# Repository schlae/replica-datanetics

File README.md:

# Replica Datanetics Keyboard

Do you need a Datanetics ASCII keyboard for your computer project (such as a replica Apple 1)? Don't want to pay high prices for an original Datanetics keyboard? Then consider building this replica.

This is not the first replica Datanetics keyboard. Mike Willegal [designed one](http://www.willegal.net/appleii/apple1-datanetics.htm). In fact, I started with his design and redid it using KiCad. Instead of using the expensive, fragile, and hard-to-find MM5740 keyboard chip, I switched to a more common microcontroller: the ATMega644P. I also removed the output buffer chips--just in case you want to redo my firmware and implement some other keyboard protocol, you'll be able to control the pin direction.

Here are the design files. The BOM does not include manufacturer part numbers because it uses very common through hole parts that you might already have. The key switches are standard Cherry MX and are available from a wide variety of sources.

[Schematic](https://github.com/schlae/replica-datanetics/blob/main/Apple1Keyb.pdf)

[Bill of Materials](https://github.com/schlae/replica-datanetics/blob/main/Apple1Keyb.csv)

[Fab Files](https://github.com/schlae/replica-datanetics/blob/main/fab/Apple1Keyb_Rev1.zip)

[Water Slide Decal Graphics](https://github.com/schlae/replica-datanetics/blob/main/keycaps.svg)

## Fabrication and Assembly Notes

The circuit board is a 2-layer board, 11.75 by 5.5 inches (298.5 x 139.7mm). No special edge connector plating or bevel is needed. To make the board look like the original, order the board "bare bones" with no solder mask or silkscreen.

**Caution: There is a "matrix" via area in the upper left corner of the board with 76 non-plated vias. The drill locations for these are included in the "Apple1Keyb-NPTH.drl" file in the fab package. The User Comments layer also includes a note to the fab vendor to NOT plate these holes. You may want to add an extra comment to your fab vendor when you put in the order that these 76 holes must not be plated.**

To assemble the board, just solder in the components. I'd recommend using a socket for the U1 microcontroller so that you can reprogram it later. The NE555 timer (U2) in the original design was meant to provide the clock for the MM5740 chip, but isn't necessary in this design. You can install it or leave it out.

The second NE555 timer (U3) is necessary for the key repeat function.

## Key Caps

The keyboard design uses standard Cherry MX key switches and keycaps are available from numerous sources. For my own build, I used DSA keycaps along with an 8U spacebar from PMK. I looked into a number of ways of putting the legends on the keycaps but I ended up having some water slide decals custom made. See the file above if you want to use this same file, but I'd recommend putting the legends closer together so they'll fit on a smaller sheet, saving you money.

## Matrix Via Area

The Datanetics design has four key switches that are not connected to the key scanning matrix and are brought out to individual pins on the edge connector. If you're building an Apple 1, you'll want to use two of these keys for the reset and clear screen functions. 

If you want keys to be included in the scanning matrix, you'll want to solder a fine wire through the appropriate via in the upper left corner of the board. To find out which key will be generated, look up the row and column number in the key\_rom array in firmware source code. You can, of course, customize the generated key by editing the source and recompiling.

## Firmware

The firmware is designed for the ATMega644P microcontroller, but it should be possible to modify it to work with other 40-pin microcontrollers in the ATMega family. The prebuilt firmware behaves like a stock MM5740.

[Prebuilt Firmware](https://github.com/schlae/replica-datanetics/blob/main/fw/apple1keyb.hex)

Be sure to set the fuse bits of the ATMega644P according to the fuses.conf file:

```
lfuse = 0x62
hfuse = 0xdd
efuse = 0xfc
```

You can build the firmware yourself pretty easily. Under Ubuntu, install the `gcc-avr` package, and build the firmware by going to the directory and typing `make`.

If you have a minipro programmer (TL866 etc) you can program the device by typing `make fuses` followed by `make prog`. For this to work correctly, you'll need the [minipro software](https://gitlab.com/DavidGriffith/minipro) installed. You could also use the Windows minipro software from the manufacturer, or another programmer entirely.

## Mechanical Brackets

[Mike Willegal's site](http://www.willegal.net/appleii/apple1-datanetics.htm) has drawings for a mechanical bracket.

## Connecting to an Apple 1

If you want to connect this keyboard to an Apple 1, you can use the following wiring diagram. The connector to use is a 30-pin 0.156" edge connector, something like EDAC 305-030-520-202 or equivalent. The DIP plug is an insulation displacement connector, something like CW CWR-130-16-0001 or equivalent.

| Edge connector pin | Description | DIP plug pin |
|--------------------|-------------|--------------|
| A | No connect (was -12V) | 11 (-12V) |
| B | Data bit 6 | 7 (B6) |
| C | Data bit 5 | 6 (B5) |
| D | Data bit 4 | 2 (B4) |
| E | Data bit 1 | 5 (B1) |
| F | Data bit 2 | 4 (B2) |
| H | Data bit 3 | 3 (B3) |
| J | Reset key | 1 (Reset) |
| K | Reset key | 9 (Gnd) |
| L | No connect (was OE) | No connect |
| M | Strobe | 14 (Str) |
| N | Data bit 7 | 8 (B7) |
| P | Data bit 8 | No connect |
| R | No connect (was data bit 9) | No connect |
| S | Ground | 9 |
| 1 | No connect | |
| 2 | No connect | |
| 3 | No connect | |
| 4 | +5V | 15, 16 |
| 5 | No connect | |
| 6 | No connect | |
| 7 | No connect | |
| 8 | Extra key 4 | 12 (Clr) |
| 9 | Extra key 4 | 16 |
| 10 | Extra key 3 | |
| 11 | Extra key 3 | |
| 12 | Extra key 1 | |
| 13 | Extra key 1 | |
| 14 | Extra key 2 | |
| 15 | Extra key 2 | |

## License
This work is licensed under a Creative Commons Attribution-ShareAlike 4.0
International License. See [https://creativecommons.org/licenses/by-sa/4.0/](https://creativecommons.org/licenses/by-sa/4.0/).

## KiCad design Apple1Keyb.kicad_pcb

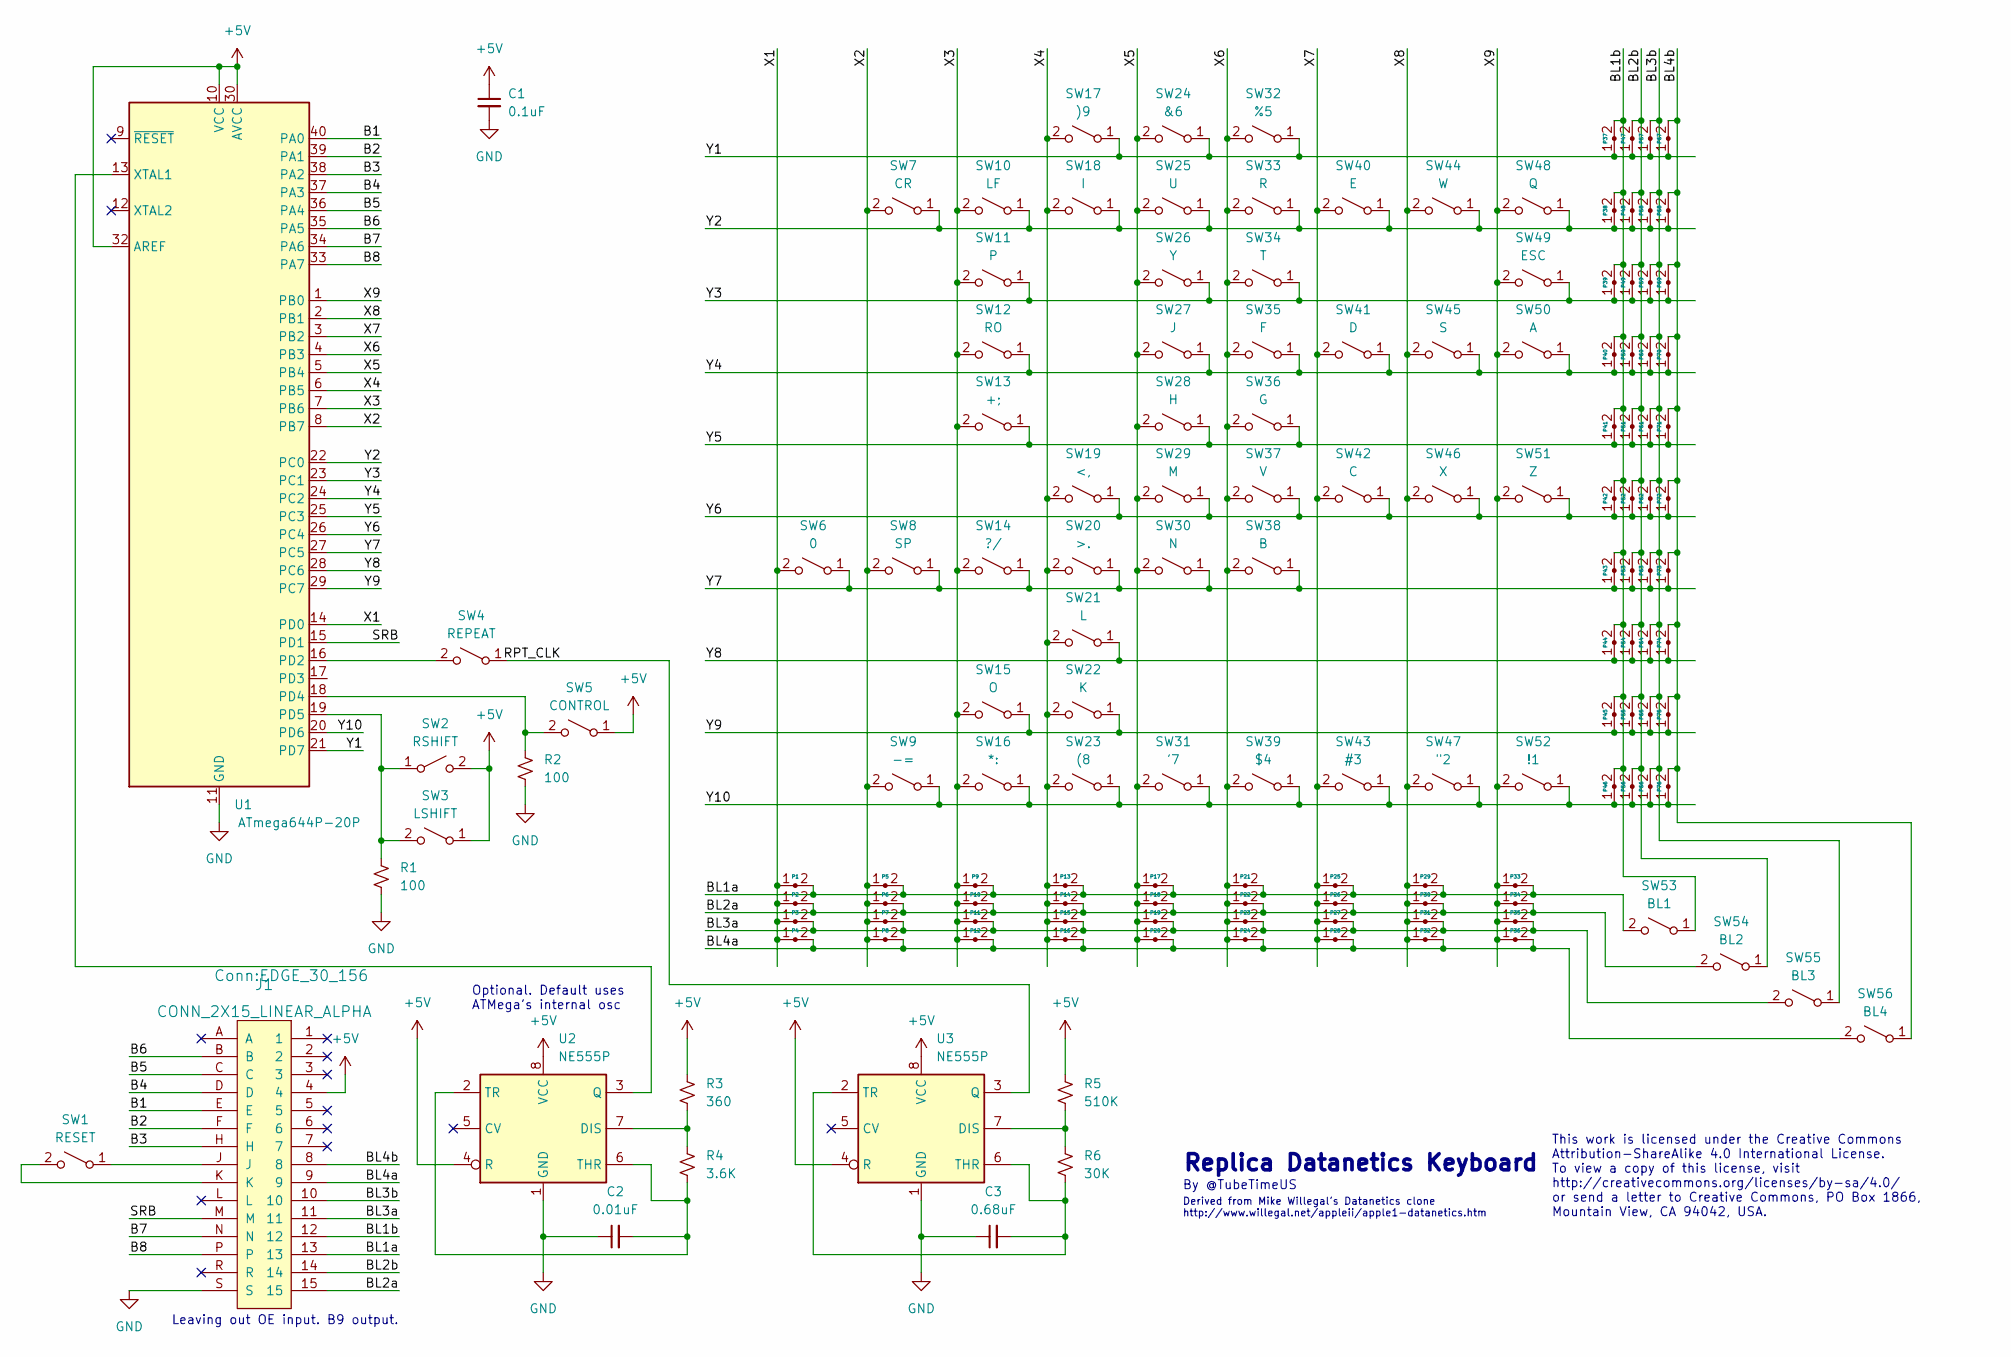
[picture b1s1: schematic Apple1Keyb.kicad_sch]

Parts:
C1: 0.1uF; C_Disc_D0.2in_W0.1in_P0.2in
C2: 0.01uF; C_Disc_D0.2in_W0.1in_P0.2in
C3: 0.68uF; C_Disc_D0.2in_W0.1in_P0.2in
J1: CONN_2X15_LINEAR_ALPHA; EDGE_30_156
P1, P2, P3, P4, P5, P6, P7, P8, P9, P10, P11, P12, P13, P14, P15, P16, P17, P18, P19, P20, P21, P22, P23, P24, P25, P26, P27, P28, P29, P30, P31, P32, P33, P34, P35, P36, P37, P38, P39, P40, P41, P42, P43, P44, P45, P46, P47, P48, P49, P50, P51, P52, P53, P54, P55, P56, P57, P58, P59, P60, P61, P62, P63, P64, P65, P66, P67, P68, P69, P70, P71, P72, P73, P74, P75, P76: jumper_pth; ViaNoPlate
R1, R2: 100; RESA500
R3: 360; RESA500
R4: 3.6K; RESA500
R5: 510K; RESA500
R6: 30K; RESA500
SW1: RESET; CHERRY_MX
SW2: RSHIFT; CHERRY_MX
SW3: LSHIFT; CHERRY_MX
SW4: REPEAT; CHERRY_MX
SW5: CONTROL; CHERRY_MX
SW6: 0; CHERRY_MX
SW7: CR; CHERRY_MX
SW8: SP; CHERRY_MX
SW9: -=; CHERRY_MX
SW10: LF; CHERRY_MX
SW11: P; CHERRY_MX
SW12: RO; CHERRY_MX
SW13: +;; CHERRY_MX
SW14: ?/; CHERRY_MX
SW15: O; CHERRY_MX
SW16: *:; CHERRY_MX
SW17: )9; CHERRY_MX
SW18: I; CHERRY_MX
SW19: <,; CHERRY_MX
SW20: >.; CHERRY_MX
SW21: L; CHERRY_MX
SW22: K; CHERRY_MX
SW23: (8; CHERRY_MX
SW24: &6; CHERRY_MX
SW25: U; CHERRY_MX
SW26: Y; CHERRY_MX
SW27: J; CHERRY_MX
SW28: H; CHERRY_MX
SW29: M; CHERRY_MX
SW30: N; CHERRY_MX
SW31: '7; CHERRY_MX
SW32: %5; CHERRY_MX
SW33: R; CHERRY_MX
SW34: T; CHERRY_MX
SW35: F; CHERRY_MX
SW36: G; CHERRY_MX
SW37: V; CHERRY_MX
SW38: B; CHERRY_MX
SW39: $4; CHERRY_MX
SW40: E; CHERRY_MX
SW41: D; CHERRY_MX
SW42: C; CHERRY_MX
SW43: #3; CHERRY_MX
SW44: W; CHERRY_MX
SW45: S; CHERRY_MX
SW46: X; CHERRY_MX
SW47: "2; CHERRY_MX
SW48: Q; CHERRY_MX
SW49: ESC; CHERRY_MX
SW50: A; CHERRY_MX
SW51: Z; CHERRY_MX
SW52: !1; CHERRY_MX
SW53: BL1; CHERRY_MX
SW54: BL2; CHERRY_MX
SW55: BL3; CHERRY_MX
SW56: BL4; CHERRY_MX
U1: ATmega644P-20P; DIP-40_W15.24mm
U2, U3: NE555P; DIP-8_W7.62mm

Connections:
+5V: C1.1, J1.4, R3.2, R5.2, SW2.2 (B), SW3.1 (A), SW5.1 (A), U1.10 (VCC), U1.30 (AVCC), U1.32 (AREF), U2.4 (R), U2.8 (VCC), U3.4 (R), U3.8 (VCC)
/B1: J1.E, U1.40 (PA0)
/B2: J1.F, U1.39 (PA1)
/B3: J1.H, U1.38 (PA2)
/B4: J1.D, U1.37 (PA3)
/B5: J1.C, U1.36 (PA4)
/B6: J1.B, U1.35 (PA5)
/B7: J1.N, U1.34 (PA6)
/B8: J1.P, U1.33 (PA7)
/BL1a: J1.13, P1.2, P5.2, P9.2, P13.2, P17.2, P21.2, P25.2, P29.2, P33.2, SW53.2 (B)
/BL1b: J1.12, P37.2, P38.2, P39.2, P40.2, P41.2, P42.2, P43.2, P44.2, P45.2, P46.2, SW53.1 (A)
/BL2a: J1.15, P2.2, P6.2, P10.2, P14.2, P18.2, P22.2, P26.2, P30.2, P34.2, SW54.2 (B)
/BL2b: J1.14, P47.2, P48.2, P49.2, P50.2, P51.2, P52.2, P53.2, P54.2, P55.2, P56.2, SW54.1 (A)
/BL3a: J1.11, P3.2, P7.2, P11.2, P15.2, P19.2, P23.2, P27.2, P31.2, P35.2, SW55.2 (B)
/BL3b: J1.10, P57.2, P58.2, P59.2, P60.2, P61.2, P62.2, P63.2, P64.2, P65.2, P66.2, SW55.1 (A)
/BL4a: J1.9, P4.2, P8.2, P12.2, P16.2, P20.2, P24.2, P28.2, P32.2, P36.2, SW56.2 (B)
/BL4b: J1.8, P67.2, P68.2, P69.2, P70.2, P71.2, P72.2, P73.2, P74.2, P75.2, P76.2, SW56.1 (A)
/RPT_CLK: SW4.1 (A), U3.3 (Q)
/SRB: J1.M, U1.15 (PD1)
/X1: P1.1, P2.1, P3.1, P4.1, SW6.2 (B), U1.14 (PD0)
/X2: P5.1, P6.1, P7.1, P8.1, SW7.2 (B), SW8.2 (B), SW9.2 (B), U1.8 (PB7)
/X3: P9.1, P10.1, P11.1, P12.1, SW10.2 (B), SW11.2 (B), SW12.2 (B), SW13.2 (B), SW14.2 (B), SW15.2 (B), SW16.2 (B), U1.7 (PB6)
/X4: P13.1, P14.1, P15.1, P16.1, SW17.2 (B), SW18.2 (B), SW19.2 (B), SW20.2 (B), SW21.2 (B), SW22.2 (B), SW23.2 (B), U1.6 (PB5)
/X5: P17.1, P18.1, P19.1, P20.1, SW24.2 (B), SW25.2 (B), SW26.2 (B), SW27.2 (B), SW28.2 (B), SW29.2 (B), SW30.2 (B), SW31.2 (B), U1.5 (PB4)
/X6: P21.1, P22.1, P23.1, P24.1, SW32.2 (B), SW33.2 (B), SW34.2 (B), SW35.2 (B), SW36.2 (B), SW37.2 (B), SW38.2 (B), SW39.2 (B), U1.4 (PB3)
/X7: P25.1, P26.1, P27.1, P28.1, SW40.2 (B), SW41.2 (B), SW42.2 (B), SW43.2 (B), U1.3 (PB2)
/X8: P29.1, P30.1, P31.1, P32.1, SW44.2 (B), SW45.2 (B), SW46.2 (B), SW47.2 (B), U1.2 (PB1)
/X9: P33.1, P34.1, P35.1, P36.1, SW48.2 (B), SW49.2 (B), SW50.2 (B), SW51.2 (B), SW52.2 (B), U1.1 (PB0)
/Y1: P37.1, P47.1, P57.1, P67.1, SW17.1 (A), SW24.1 (A), SW32.1 (A), U1.21 (PD7)
/Y2: P38.1, P48.1, P58.1, P68.1, SW7.1 (A), SW10.1 (A), SW18.1 (A), SW25.1 (A), SW33.1 (A), SW40.1 (A), SW44.1 (A), SW48.1 (A), U1.22 (PC0)
/Y3: P39.1, P49.1, P59.1, P69.1, SW11.1 (A), SW26.1 (A), SW34.1 (A), SW49.1 (A), U1.23 (PC1)
/Y4: P40.1, P50.1, P60.1, P70.1, SW12.1 (A), SW27.1 (A), SW35.1 (A), SW41.1 (A), SW45.1 (A), SW50.1 (A), U1.24 (PC2)
/Y5: P41.1, P51.1, P61.1, P71.1, SW13.1 (A), SW28.1 (A), SW36.1 (A), U1.25 (PC3)
/Y6: P42.1, P52.1, P62.1, P72.1, SW19.1 (A), SW29.1 (A), SW37.1 (A), SW42.1 (A), SW46.1 (A), SW51.1 (A), U1.26 (PC4)
/Y7: P43.1, P53.1, P63.1, P73.1, SW6.1 (A), SW8.1 (A), SW14.1 (A), SW20.1 (A), SW30.1 (A), SW38.1 (A), U1.27 (PC5)
/Y8: P44.1, P54.1, P64.1, P74.1, SW21.1 (A), U1.28 (PC6)
/Y9: P45.1, P55.1, P65.1, P75.1, SW15.1 (A), SW22.1 (A), U1.29 (PC7)
/Y10: P46.1, P56.1, P66.1, P76.1, SW9.1 (A), SW16.1 (A), SW23.1 (A), SW31.1 (A), SW39.1 (A), SW43.1 (A), SW47.1 (A), SW52.1 (A), U1.20 (PD6)
GND: C1.2, C2.1, C3.1, J1.S, R1.1, R2.1, U1.11 (GND), U1.31 (GND), U2.1 (GND), U3.1 (GND)
unnamed: C2.2, R4.1, U2.2 (TR), U2.6 (THR)
unnamed: C3.2, R6.1, U3.2 (TR), U3.6 (THR)
unnamed: J1.J, SW1.1 (A)
unnamed: J1.K, SW1.2 (B)
unnamed: R1.2, SW2.1 (A), SW3.2 (B), U1.19 (PD5)
unnamed: R2.2, SW5.2 (B), U1.18 (PD4)
unnamed: R3.1, R4.2, U2.7 (DIS)
unnamed: R5.1, R6.2, U3.7 (DIS)
unnamed: SW4.2 (B), U1.16 (PD2)
unnamed: U1.13 (XTAL1), U2.3 (Q)

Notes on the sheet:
By @TubeTimeUS
Leaving out OE input. B9 output.
Optional. Default uses ATMega's internal osc
Derived from Mike Willegal's Datanetics clone http://www.willegal.net/appleii/apple1-datanetics.htm
Replica Datanetics Keyboard
This work is licensed under the Creative Commons Attribution-ShareAlike 4.0 International License. To view a copy of this license, visit http://creativecommons.org/licenses/by-sa/4.0/ or send a letter to Creative Commons, PO Box 1866, Mountain View, CA 94042, USA.

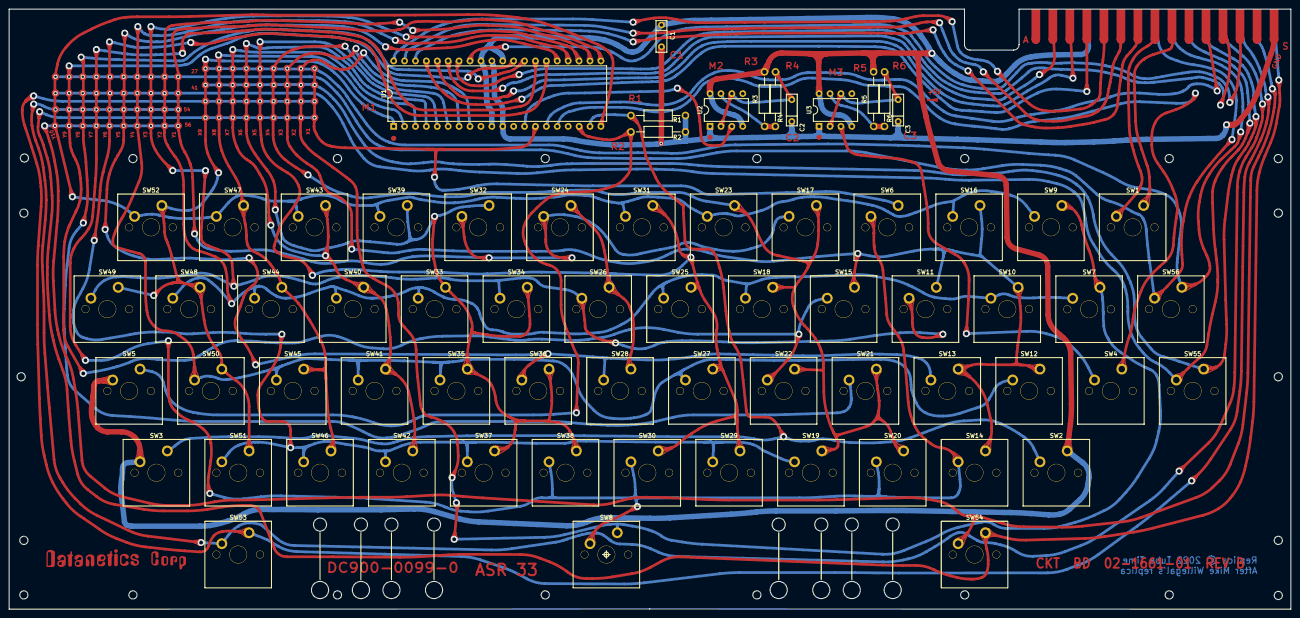
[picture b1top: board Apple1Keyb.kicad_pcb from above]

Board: 2 copper layers, 298.4 x 139.7 mm, 169 parts (1 on the bottom side), 49 nets.

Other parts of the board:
G1: LOGO; Datanetics
MH1, MH2, MH3, MH4, MH5, MH6, MH7, MH8, MH9, MH10, MH11, MH12, MH13, MH14, MH15, MH16, MH17, MH18, MH19, MH20, MH21, MH22: MountHole
ST1: CHERRY_ST3

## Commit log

2022-12-15 Initial empty commit.
2022-12-15 Initial version.
2022-12-17 Fix equals key
2022-12-17 Add wiring for Apple 1

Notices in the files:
Apple1Keyb.kicad_pcb:
Copyright (C) 2022 Tube Time
Replica © 2022 Tube Time
